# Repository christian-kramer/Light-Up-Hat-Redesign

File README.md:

# Light-Up-Hat-Redesign
Putting wearable technology in a winter hat

---

Most people, when talking about "hats" in the hobbyist embedded world, are referring to little devices that fit on top of a Raspberry Pi. But no, I'm talking about an actual hat... like the one that goes on your head.

It all starts with a mistake; letting my winter hat with a built-in headlamp go through my wash without taking the electronics out first.

Now, these things aren't terribly expensive to replace. Mine was just $13 on Amazon.

But being savvy with electronics, I decided I wanted to try to fix mine. But... what I found was rather disheartening.

These things are cheap for a reason, and that reason is they're not very well built. The wires of the battery pack were just barely soldered onto the LED contacts to begin with... any fix I did to this thing was still going to be temporary. Add to that the annoyance of having to turn the switch on the battery pack off with my fingernail, and... I smelled an opportunity for an improvement. To the drawing board!

I knew I wanted to keep the "5-LED array" form factor, but I also wanted a button next to the LEDs I could push to toggle them on and off, so I didn't have to take off my gloves like I currently had to do. I spent a lot of time trying to figure out an all-analog method of doing this push button that didn't require many components. But in the end, I decided I should use up those PIC10F220s I had ordered for my first-ever circuit boards I designed a year ago.

Here's what I came up with for a board:

First off, we've got some nice big through-hole pads for the battery wires to connect to. I want to be able to yank on those things without even budging. Next, we've got the on/off push-button. I decided to use these silicone "soundless tact switches" in place of the typical clicky kind. That way I didn't have to use much force, allowing me to keep my gloves on.

The battery leads into the nifty XC6206 SOT-23 3.3v regulator I found on eBay from Torex. At $0.40, they're a steal to save some space.

The regulator then leads into the ever-faithful PIC10F220, which handles the input of the button and also controls a 2n3906 PNP transistor, also in a SOT-23 package. This drives the 5 LEDs, which should give us plenty of light!

Finally, everything arrived in the mail.

The boards turned out great! I opted for black so it would match the hat color, and because I absolutely love JLCPCB's matte black solder mask.

On to assembly!

Once everything was put together... it didn't work! No matter what I did, the PIC10F220 just wouldn't talk to my PC! I was starting to have flashbacks to a year ago, when I tried using these PICs for the first time. Maybe I had a bad batch?

I refused to believe that. First thing I did was check to ensure all 6 pins had good contact with the traces... and what do you know! Pin 1, the programming Data Pin, wasn't soldered properly underneath. After some solder paste and a reflow, the PIC talked! So, I whipped up a quick program to turn on the PNP transistor, and... nothing. No light. What gives? I used my multimeter again, which was showing  0v at the base, 3.3v at the emitter, and... 0v at the collector. With a 1KΩ base resistor, there should certainly be enough current flowing to achieve saturation. What in the world? Is my understanding of how transistors work flawed? I pored for hours over schematics and reference designs, trying to figure out why my 2n3906 wasn't turning on. And then, I happened to glance at a diagram for the SOT-23 package pinout.

I had to do a double-take. Wait, the base is on the *left*?! Oh no, I designed the board with the base on the right!

The SOT-23 version's base and emitter are swapped from the TO-92 version's. Gah! What do I do now?

Funny enough, this is actually a common design error, even amongst professionals. So common, in fact, that they apparently make reversed versions of SOT-23 BJTs for exactly this occasion, (though probably for cases where re-spinning boards would cost $$$). A hobbyist-level fix is actually to bend the pins and flip the transistor upside-down. Which worked! The LEDs turned on!

Unfortunately, soon after, I accidentally connected the power leads incorrectly, and destroyed the board with 6 volts reverse polarity. But when I tried assembling another board, two of the PIC10F220's pins bridged with solder. Try as I might, I couldn't get them un-bridged... so I tried making *another*. But that one bridged too! At this point, I got so frustrated I gave up on hand-assembling, and decided to try out a new feature of JLCPCB: their SMT Assembly Service.

The way it works is  you go to [this](https://jlcpcb.com/client/index.html#/parts/componentSearch) page and find each component you need in your schematic. When you click on one, it will give you the description, datasheet, and "LCSC Part #". This part number is what you will specify in your schematic symbol's properties, as "LCSC".

At the end of your design process, when you're ready to export your files for manufacture, there are some extra steps to follow for providing the part coordinates and tooling holes needed, which JLCPCB explains [here](https://support.jlcpcb.com/category/78-smt-assembly).

Finally, the boards arrived, and they looked great! Everything was assembled except for the LEDs, button, and battery pack. And I needed to program them too, of course.

Video of it working on my bench: https://i.imgur.com/HR5HdYS.mp4

Video of it working on my bench, with battery pack: https://i.imgur.com/gJqf0xF.mp4

Video of completed hat (WARNING: Very bright and flashing lights!): https://i.imgur.com/4RvkQvS.mp4

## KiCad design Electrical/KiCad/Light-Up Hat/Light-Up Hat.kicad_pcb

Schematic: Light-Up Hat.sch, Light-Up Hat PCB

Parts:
BT1: Battery_Cell; SolderWirePad_1x02_P5.08mm_Drill1.5mm
C1, C2: 1μF; C_0805_2012Metric; LCSC C28323
C3: C_Small; C_0805_2012Metric; LCSC C49678
D1, D2, D3, D4, D5: LED; LED_D5.0mm
J1: Conn_01x04; PinHeader_1x04_P2.54mm_Vertical
Q1: MMBT3906; SOT-23; LCSC C2143
R1: 1KΩ; R_0805_2012Metric; LCSC C17513
SW1: SW_SPST; SW_PUSH_8mm_H5mm
U1: XC6206; SOT-23; LCSC C5446
U2: PIC10F200-IOT; SOT-23-6; LCSC C8224

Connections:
+3V3: C2.1, C3.1, Q1.2 (E), U1.2 (VO), U2.5
+BATT: BT1.1, C1.1, U1.3 (VI)
/BUTTON_INPUT: J1.4, SW1.1, U2.3
/ICSPDAT: J1.3, U2.1
/LED_CONTROL: R1.2, U2.4
GND: BT1.2, C1.2, C2.2, C3.2, D1.1, D2.1, D3.1, D4.1, D5.1, J1.2, SW1.2, U1.1 (GND), U2.2
unnamed: D1.2, D2.2, D3.2, D4.2, D5.2, Q1.3 (C)
unnamed: Q1.1 (B), R1.1
VPP: J1.1, U2.6

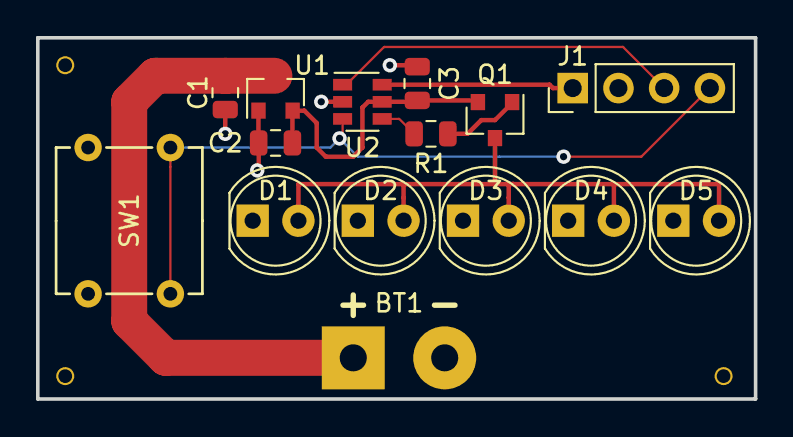
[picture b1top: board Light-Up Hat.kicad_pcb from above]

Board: 2 copper layers, 39.9 x 20.1 mm, 15 parts (0 on the bottom side), 9 nets.

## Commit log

2019-10-20 rough draft of design without values
2019-10-31 PCB For Manufacture
2019-11-17 Hat LEDs blink on and off every 1 second
2019-11-17 attempt to correct linguist reporting
2019-11-17 fixed file extension
2019-12-05 fixed board design for new revision
2019-12-05 working firmware for on, off, emergency mode
